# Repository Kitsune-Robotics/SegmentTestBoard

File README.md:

# SegmentTestBoard

The segment test board is a small board comprising the
[SN74HC595](https://www.lcsc.com/product-detail/Shifting-Register_Texas-Instruments-SN74HC595PWR_C273642.html) shift register,
and the [SM420391N](https://www.lcsc.com/product-detail/Led-Segment-Display_ARKLED-Wuxi-ARK-Tech-Elec-SM420391N-8_C252199.html) led seven segment display.

If you're looking for the latest docs/builds, see our [Releases Page](https://github.com/KenwoodFox/SegmentTestBoard/releases).

# Getting Started

First, clone this repo (and optionally checkout a branch)

```shell
git clone https://github.com/KenwoodFox/SegmentTestBoard.git
cd SegmentTestBoard
```

# Init Submodules

Some libraries and resources are included as submodules, run the following
command to initialize them before opening the main sch

(If you get a missing library error, make sure to do this)

```shell
git submodule update --init --recursive
```

## Project Layout

If you want to use this project template for yourself, you can find it [here!](https://github.com/KenwoodFox/Project-Template)

# License

License is BSD(2)

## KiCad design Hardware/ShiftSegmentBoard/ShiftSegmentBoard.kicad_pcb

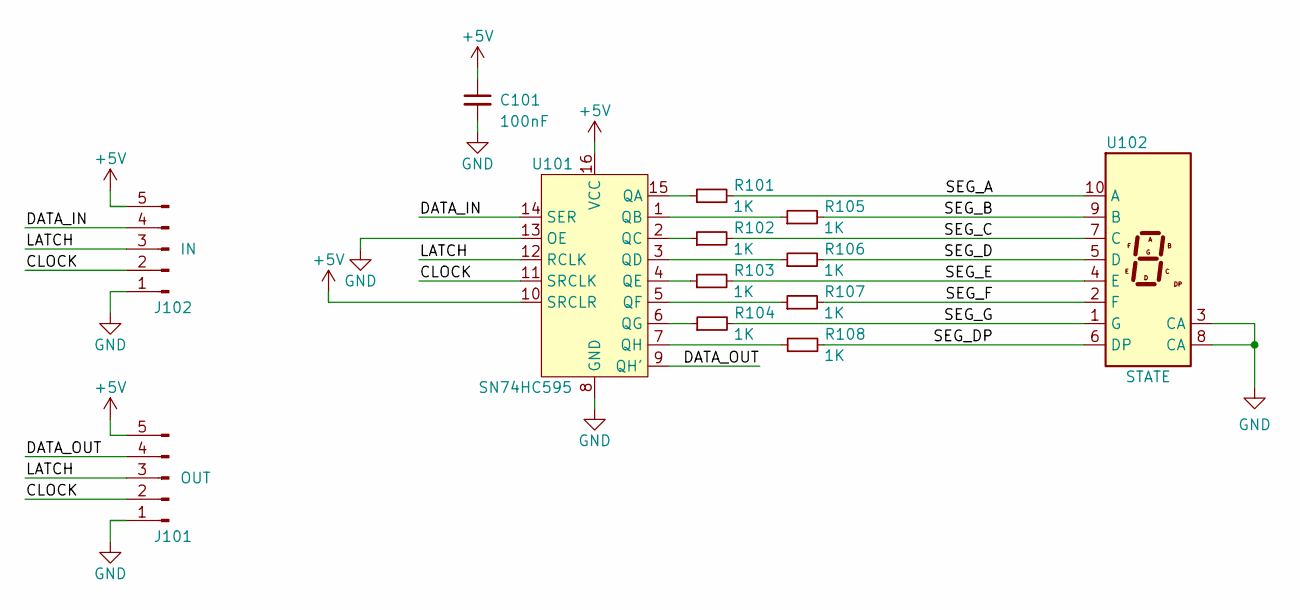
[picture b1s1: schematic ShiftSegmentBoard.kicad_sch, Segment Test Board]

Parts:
C101: 100nF; C_0805_2012Metric
J101: OUT; PinHeader_1x05_P2.54mm_Vertical
J102: IN; PinHeader_1x05_P2.54mm_Vertical
R101, R102, R103, R104, R105, R106, R107, R108: 1K; R_0805_2012Metric
U101: SN74HC595
U102: STATE; SM420391N8

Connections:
+5V: C101.1, J101.5, J102.5, U101.10 (SRCLR), U101.16 (VCC)
/CLOCK: J101.2, J102.2, U101.11 (SRCLK)
/DATA_IN: J102.4, U101.14 (SER)
/DATA_OUT: J101.4, U101.9 (QH')
/LATCH: J101.3, J102.3, U101.12 (RCLK)
/SEG_A: R101.2, U102.10 (A)
/SEG_B: R105.2, U102.9 (B)
/SEG_C: R102.2, U102.7 (C)
/SEG_D: R106.2, U102.5 (D)
/SEG_DP: R108.2, U102.6 (DP)
/SEG_E: R103.2, U102.4 (E)
/SEG_F: R107.2, U102.2 (F)
/SEG_G: R104.2, U102.1 (G)
GND: C101.2, J101.1, J102.1, U101.8 (GND), U101.13 (OE), U102.3 (CA), U102.8 (CA)
unnamed: R101.1, U101.15 (QA)
unnamed: R105.1, U101.1 (QB)
unnamed: R102.1, U101.2 (QC)
unnamed: R106.1, U101.3 (QD)
unnamed: R103.1, U101.4 (QE)
unnamed: R107.1, U101.5 (QF)
unnamed: R104.1, U101.6 (QG)
unnamed: R108.1, U101.7 (QH)

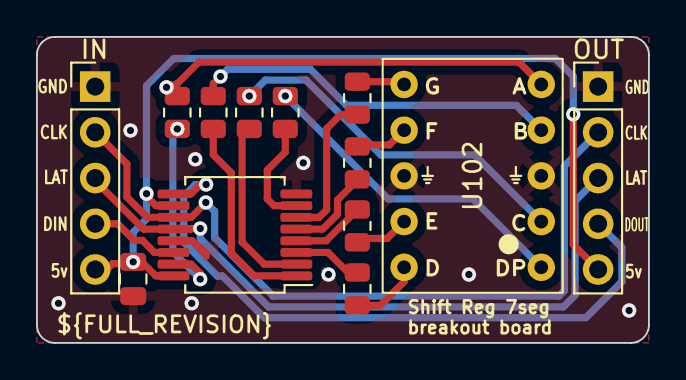
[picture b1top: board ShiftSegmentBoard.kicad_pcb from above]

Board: 2 copper layers, 34.0 x 17.0 mm, 13 parts (0 on the bottom side), 22 nets.

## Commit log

2023-04-16 init to commit it
2023-04-16 Add revision to silkscreen
2023-04-16 use correct pinheaders
2023-04-17 Add final bits
2023-10-15 Update from template
2023-10-15 Remove docs
2023-10-15 Add library boilerplate
2023-10-15 move and repair
2023-10-16 Library works
2023-10-16 Add letter shortcuts
2023-10-16 Add decimal controls
2023-10-16 Add cover image
2023-10-16 Add badges in readme
2023-10-16 add blank shortcut
2023-11-23 Add raw function
